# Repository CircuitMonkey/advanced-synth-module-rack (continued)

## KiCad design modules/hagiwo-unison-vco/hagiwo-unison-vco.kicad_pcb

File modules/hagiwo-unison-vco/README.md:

# Hagiwo Unison VCO -- module for ASMR
This module is based on [a design](https://note.com/solder_state/n/na0ae5754fa9c) by Japanese engineer "[Hagiwo](https://note.com/solder_state)".  This ASMR module is derived from the EuroRack version of their module.

## About
The Unison is based on the Arduino compatible [Seeed XIAO RA4M1](https://www.seeedstudio.com/Seeed-XIAO-RA4M1-p-5943.html) processor module featuring two oscillators and wavetable. Amazingly, it is touted as having a total BOM cost of about $9 in prototype form. Another benefit of the RA4M1 based Unison module is that experimenters can study and modify the open source code that generates the functionality of the module.

## What is ASMR?
[ASMR -- Advanced Synth Module Rack System](https://github.com/CircuitMonkey/advanced-synth-module-rack).  A modern alternative to Eurorack.

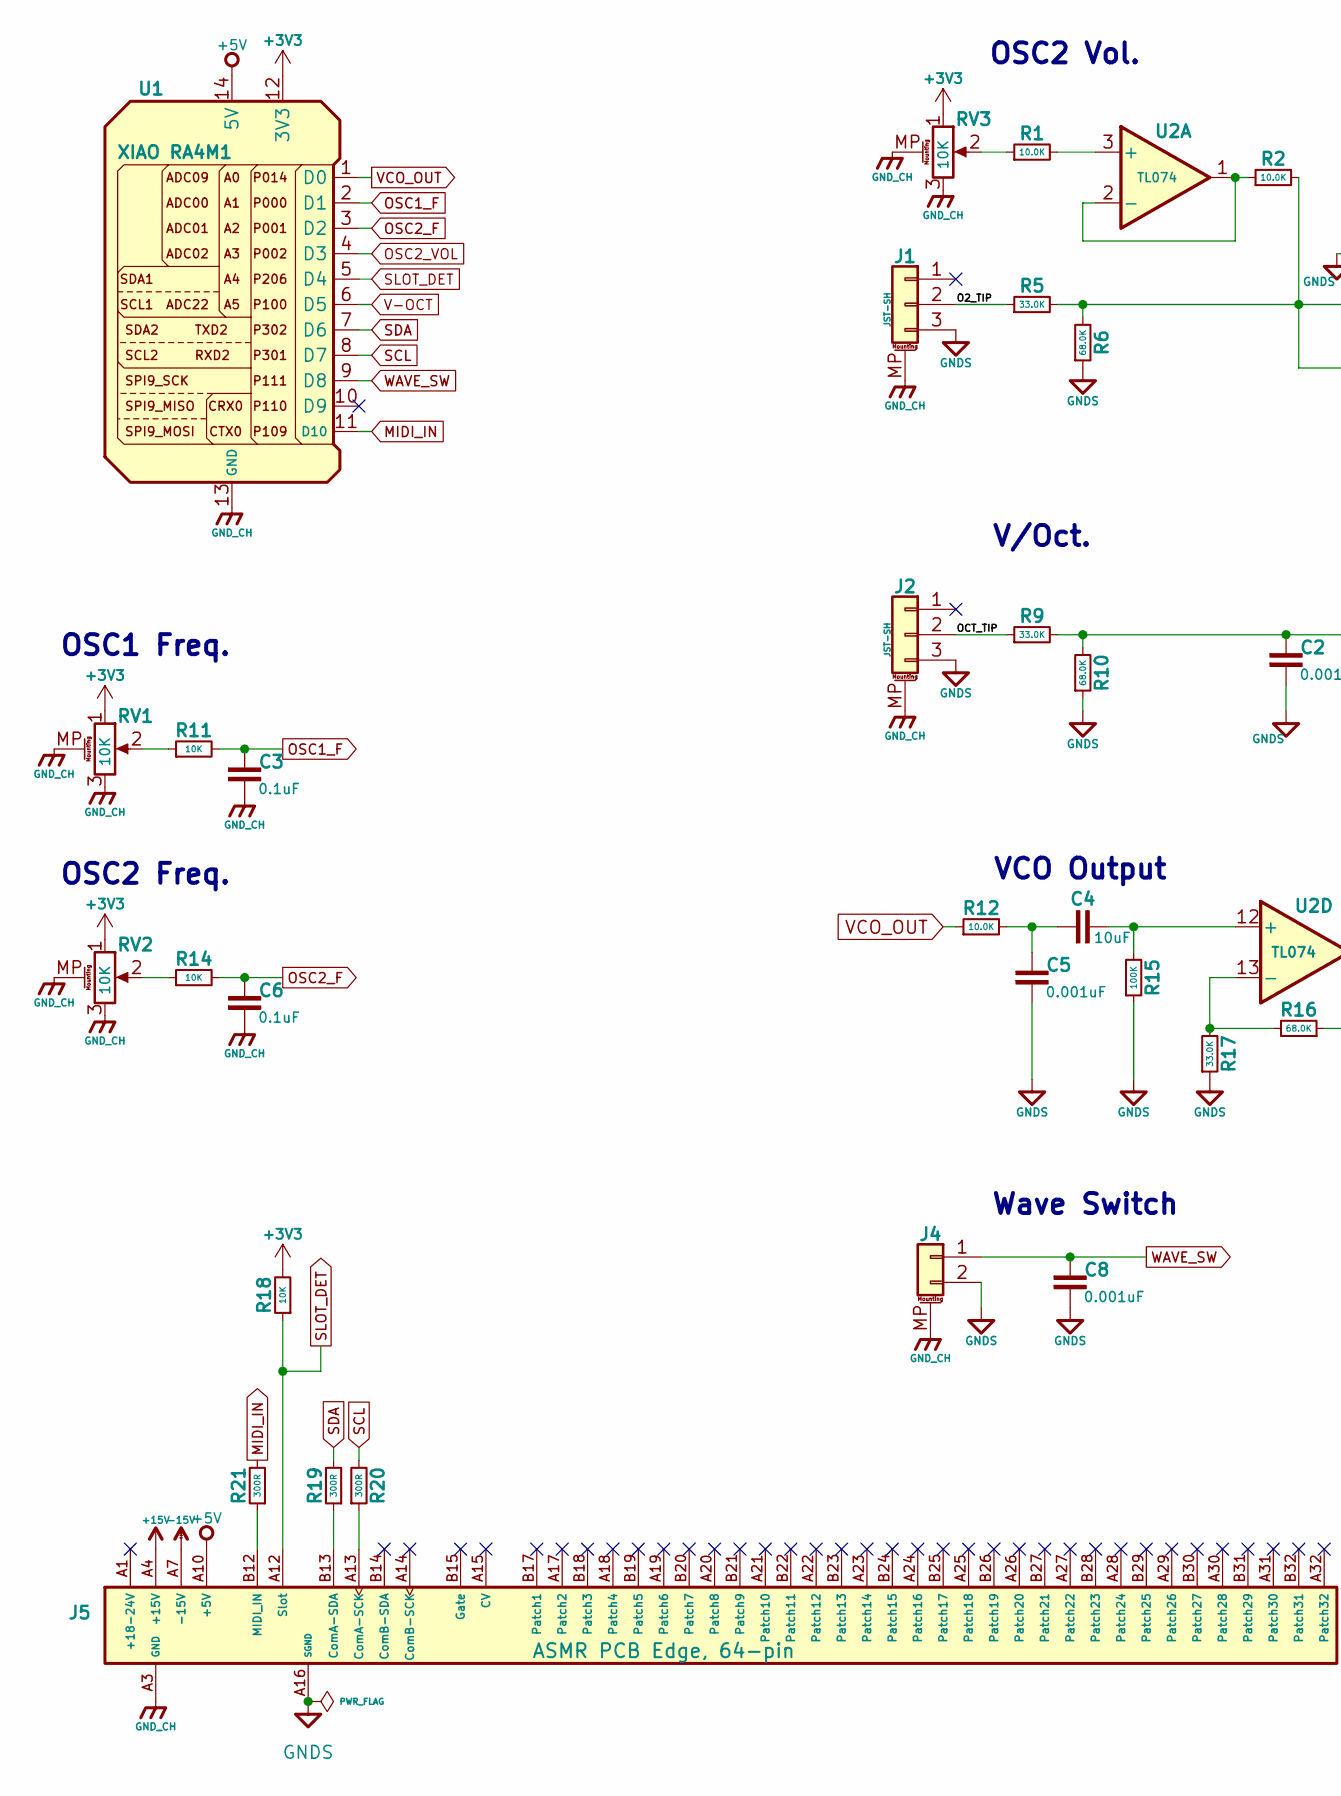
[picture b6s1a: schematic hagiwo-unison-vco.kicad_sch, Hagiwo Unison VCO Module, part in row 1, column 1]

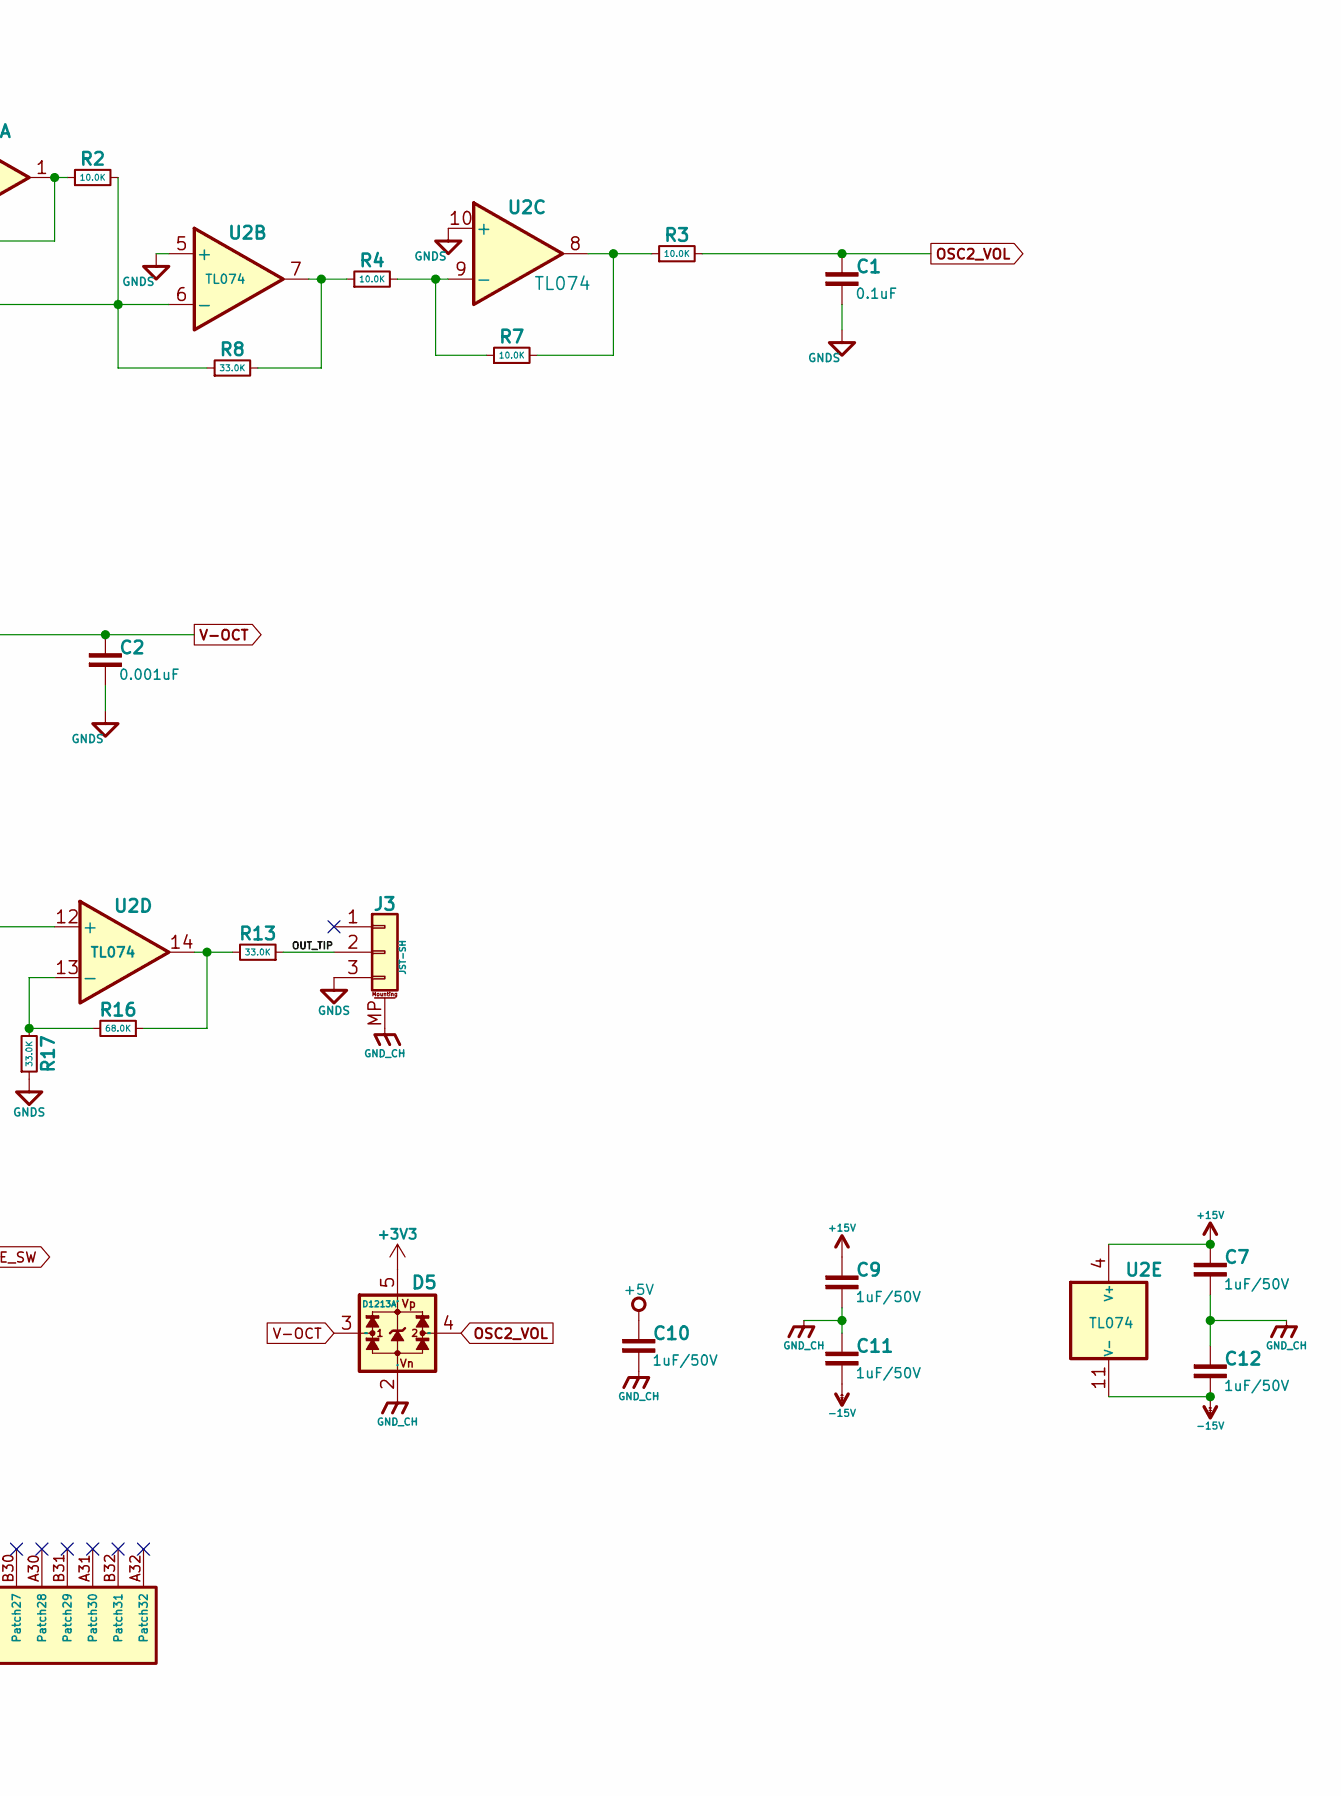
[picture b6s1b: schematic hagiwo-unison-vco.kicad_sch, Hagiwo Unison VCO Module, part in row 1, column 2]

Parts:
C1, C3, C6: 0.1uF; C_0603_1608Metric
C2, C5, C8: 0.001uF; C_0603_1608Metric
C4: 10uF; C_0603_1608Metric
C7, C9, C10, C11, C12: 1uF/50V; C_0603_1608Metric
D5: D1213A; SOT-25; MPN D1213A-02SM
J1, J2, J3: JST-SH; JST_SH_BM03B-SRSS-TB_1x03-1MP_P1.00mm_Vertical
J4: Conn_01x02_MountingPin; JST_SH_BM02B-SRSS-TB_1x02-1MP_P1.00mm_Vertical
J5: ASMR-Edge-64
R1, R2, R3, R4, R7, R12: 10.0K; R_0603_1608Metric
R5, R8, R9, R13, R17: 33.0K; R_0603_1608Metric
R6, R10, R16: 68.0K; R_0603_1608Metric
R11, R14, R18: 10K; R_0603_1608Metric
R15: 100K; R_0603_1608Metric
R19, R20, R21: 300R; R_0603_1608Metric
RV1, RV2, RV3: 10K; pot-thd-ra-11mm
U1: XIAO RA4M1; XIAO-14P-SMD-2.54-21X17.8MM
U2: TL074; SO-14_3.9x8.65mm_P1.27mm; MPN TL074HIDR

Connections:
+3V3: D5.5 (Vp), R18.2, RV1.1, RV2.1, RV3.1, U1.12 (3V3)
+5V: C10.1, J5.A10 (+5V), J5.A11 (+5V), J5.B10 (+5V), J5.B11 (+5V), U1.14 (5V)
+15V: C7.1, C9.1, J5.A4 (+15V), J5.A5 (+15V), J5.B4 (+15V), J5.B5 (+15V), U2.4 (V+)
-15V: C11.2, C12.2, J5.A7 (-15V), J5.A8 (-15V), J5.B7 (-15V), J5.B8 (-15V), U2.11 (V-)
/O2_TIP: J1.2, R5.1
/OCT_TIP: J2.2, R9.1
/OUT_TIP: J3.2, R13.1
GNDS: C1.2, C2.2, C5.2, C8.2, J1.3, J2.3, J3.3, J4.2, J5.A16 (SGND), J5.B16 (SGND), R6.1, R10.1, R15.1, R17.1, U2.5 (+), U2.10 (+)
GND_CH: C3.2, C6.2, C7.2, C9.2, C10.2, C11.1, C12.1, D5.2 (Vn), J1.MP (MountPin), J2.MP (MountPin), J3.MP (MountPin), J4.MP (MountPin), J5.A3 (GND), J5.A6 (GND), J5.A9 (GND), J5.B3 (GND), J5.B6 (GND), J5.B9 (GND), RV1.3, RV1.MP (MountPin), RV2.3, RV2.MP (MountPin), RV3.3, RV3.MP (MountPin), U1.13 (GND)
MIDI_IN: R21.2, U1.11 (D10)
unnamed: C4.1, C5.1, R12.2
unnamed: J5.A13 (ComA-SCK), R20.1
unnamed: J5.B13 (ComA-SDA), R19.1
unnamed: J5.B12 (MIDI_IN), R21.1
unnamed: R1.1, RV3.2
unnamed: R3.1, R7.2, U2.8
unnamed: R4.1, R8.2, U2.7
unnamed: R11.1, RV1.2
unnamed: R13.2, R16.1, U2.14
unnamed: R14.1, RV2.2
unnamed: R1.2, U2.3 (+)
unnamed: R2.1, U2.1, U2.2 (-)
unnamed: R2.2, R5.2, R6.2, R8.1, U2.6 (-)
unnamed: R4.2, R7.1, U2.9 (-)
unnamed: C4.2, R15.2, U2.12 (+)
unnamed: R16.2, R17.2, U2.13 (-)
OSC1_F: C3.1, R11.2, U1.2 (D1)
OSC2_F: C6.1, R14.2, U1.3 (D2)
OSC2_VOL: C1.1, D5.4 (CH2), R3.2, U1.4 (D3)
SCL: R20.2, U1.8 (D7)
SDA: R19.2, U1.7 (D6)
SLOT_DET: J5.A12 (Slot), R18.1, U1.5 (D4)
V-OCT: C2.1, D5.3 (CH1), R9.2, R10.2, U1.6 (D5)
VCO_OUT: R12.1, U1.1 (D0)
WAVE_SW: C8.1, J4.1, U1.9 (D8)

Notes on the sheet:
OSC1 Freq.
OSC2 Vol.
Wave Switch
V/Oct.
OSC2 Freq.
VCO Output

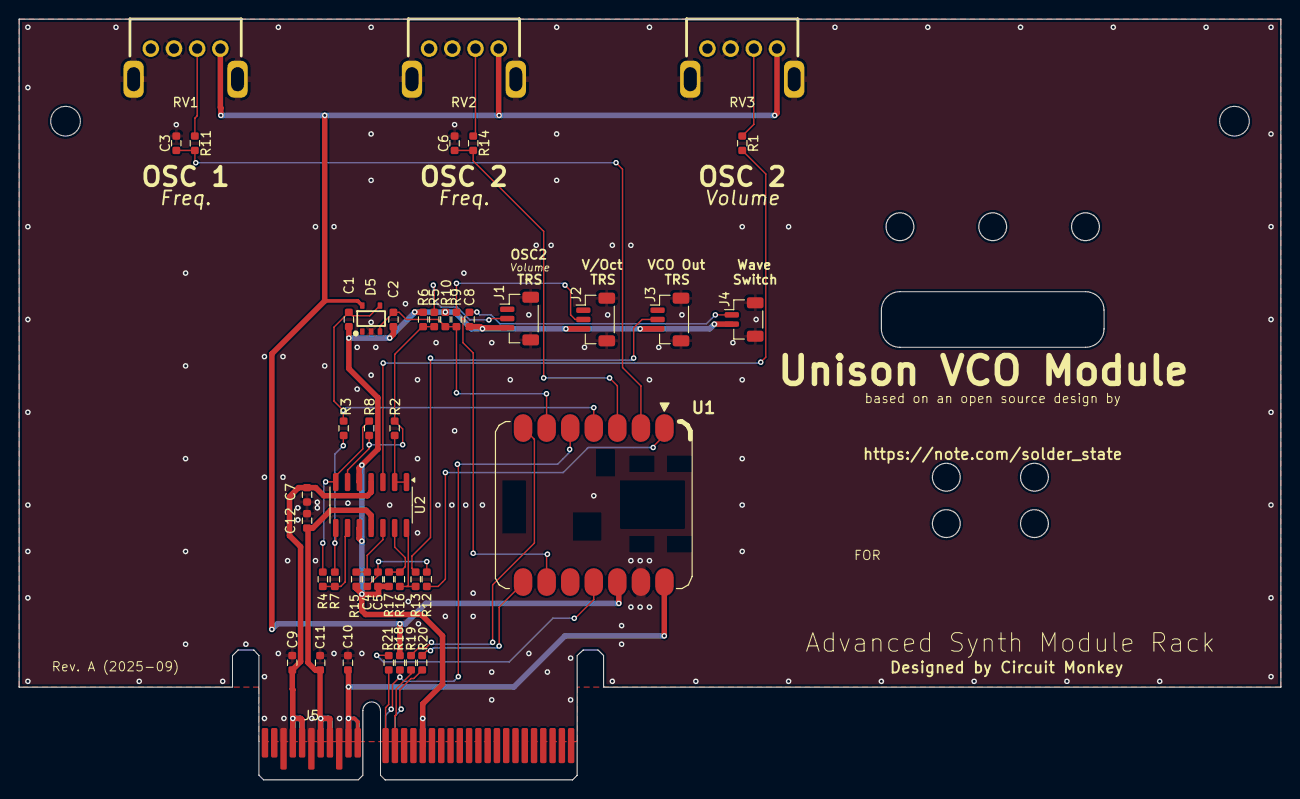
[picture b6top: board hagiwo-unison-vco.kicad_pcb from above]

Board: 2 copper layers, 136.0 x 82.0 mm, 44 parts (0 on the bottom side), 35 nets.

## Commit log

2025-08-12 Add Backplane Reference Design
2025-08-12 Add Module PCB Reference Design
2025-08-12 Add Face plate reference design.
2025-08-12 Copy Reference Designs for Power Supply Design
2025-08-15 First pass on the power supply module.
2025-08-16 Redesign backplane for 64 pin connector.
2025-08-17 Update design with 64 pin PCI connector.
2025-08-17 Update reference design for 64-pin edge connector.
2025-08-18 Add reference dims for LEDs and USB connector.
2025-08-18 Create faceplate for ASMR power supply module.
2025-08-21 Excuse some DRC issues.
2025-08-22 Create DreamLand prototyping PCB
2025-08-22 Update/improve symbol for ASMR edge.
2025-08-22 More changes to DreamLand.
2025-08-22 Move DreamLand to a sub-dir.
2025-08-22 Copy Reference face plate for DreamLand module.
2025-08-22 Designed DreamLand face plate.
2025-08-23 Final DreamLand faceplate?
2025-08-23 Tune faceplate design.
2025-08-23 Tune Aesthetic of face plate.
2025-08-25 Add width dimension for inner chassis.
2025-08-30 Create VCO module based on Hagiwo design.
2025-08-31 Updates to Unison board.
2025-09-08 New design based on Hagiwo MOD2.
2025-09-09 Bench Buddy PCB Added
2025-09-09 Fix text error in document legend.
2025-09-09 Gerber settings added.
2025-09-09 Ignore gerber dir.
2025-09-09 Tune final power supply design.
2025-09-09 Gerber settings.
2025-09-09 DRC warning.
2025-09-09 Rename project.
2025-09-09 Gerber settings and more PCB silk changes.
2025-09-09 Final tuning for power supply.
2025-09-09 Final Gerber tunings.
2025-09-09 Gerber tunings.
2025-09-09 Move DreamLand to Modules dir.
2025-09-09 Remove unused project.
2025-09-09 Tune legend text.
2025-09-09 Final tuning for DreamLand
2025-09-09 Update Gerber settings.
2025-09-09 Final design tuning.
2025-09-09 Final tuning and gerber settings.
2025-09-09 Tune deisgn.
2025-09-10 Add JLC PCB serial tag to back silk.
2025-09-10 Add JLC PCB serial tag to back of PCB
2025-09-10 Gerbers for PCBs submitted on 9-SEP-2025
2025-10-05 Rev.B Notes and changes. Work in Progress.
2025-10-05 Rev.A schematic
2025-10-05 Update to proper slot detect resistor values.
2025-10-05 Add some BOM creation settings.
2025-10-05 Add Rev.B notes and changes. Work in progress.
2025-10-05 Create basic OLED module tester.
2025-10-05 Create working MOD2 VCO code.
2025-11-04 Rev.B Tuning. Part values mostly.
2025-11-23 Remove unused Unison VCO design. MOD2 design is preferred.
2025-11-29 Adapted VCO code for LFO module.
2025-11-30 Added random tone mode. Improve comments.
